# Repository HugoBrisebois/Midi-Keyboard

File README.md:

## Midi-Keyboard

This is my first hardware project. A small and Functional Midi Keyboard

# renders of the project

# features
This Midi Keyboard has two potentiometers, 30 keys for the keyboard itself and for other settings!
- output for AUX
- powered by the Orpheus pico made by Hackclub
- LCD display for menus and feedback
- Custom PCB
- Custom Case

# Software used
- kicad 9.0
- fusion 360
- hackclub Slack for help and questions
- mouser.ca for screws

# Why I made it
I made this Project for Blueprint Hackclub which is a hardware YSWS (You Ship, We Ship) where I will get a grant to buy all the parts I need to build. i built this to get a feel for the YSWS and to learn some hardware

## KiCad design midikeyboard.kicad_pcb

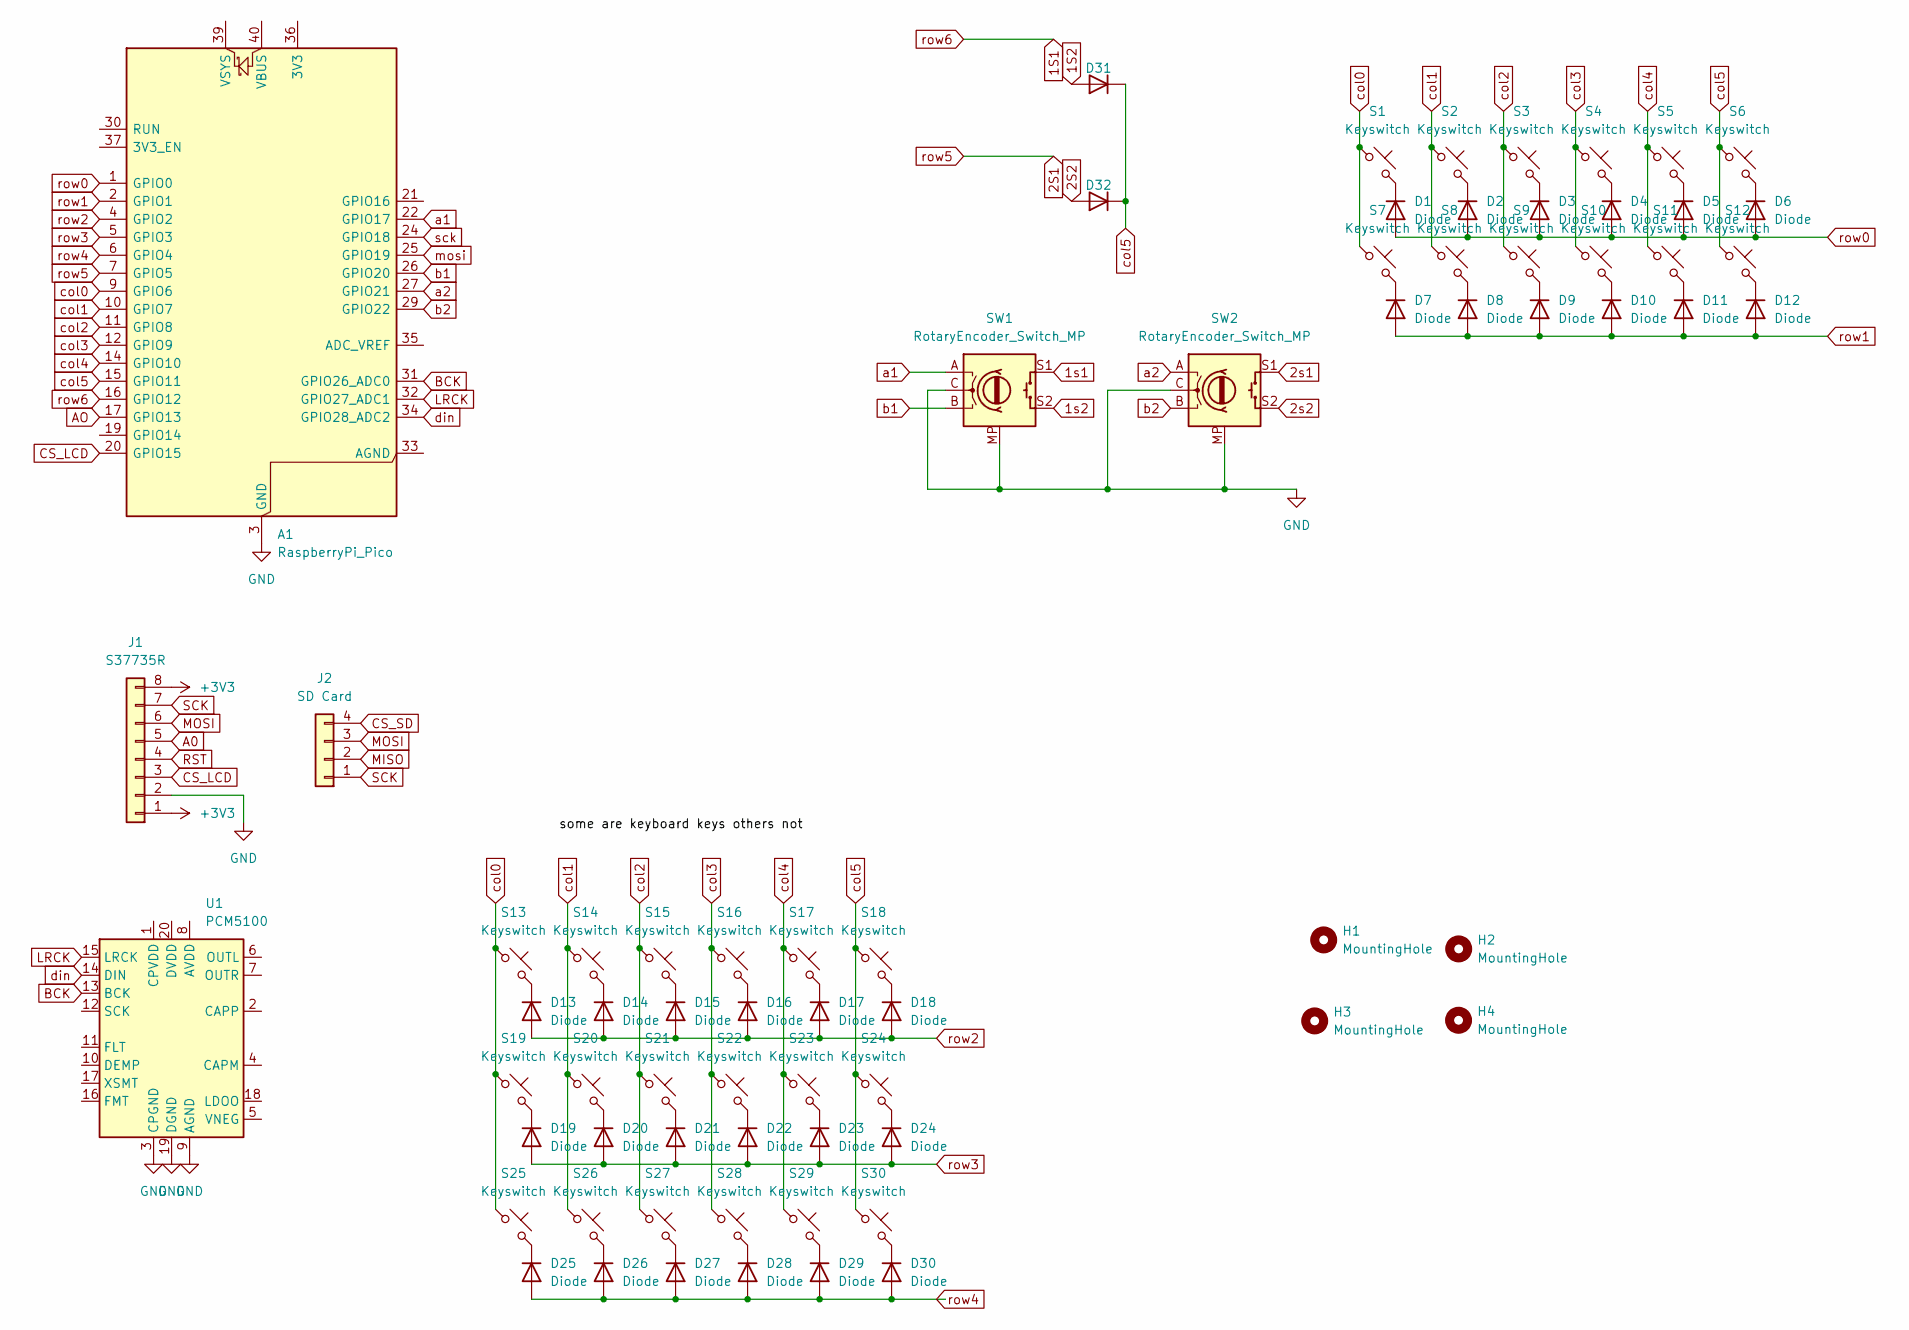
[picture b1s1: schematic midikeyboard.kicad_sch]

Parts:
A1: RaspberryPi_Pico; RaspberryPi_Pico_Common_Unspecified
D1, D2, D3, D4, D5, D6, D7, D8, D9, D10, D11, D12, D13, D14, D15, D16, D17, D18, D19, D20, D21, D22, D23, D24, D25, D26, D27, D28, D29, D30: Diode; Diode_DO-35
D31, D32: 1N4148; Diode_DO-35
H1, H2, H3, H4: MountingHole; MountingHole_3.2mm_M3
J1: S37735R; PinSocket_1x08_P2.54mm_Vertical
J2: SD Card; PinSocket_1x04_P2.54mm_Vertical
S1, S2, S3, S4, S5, S6, S7, S8, S9, S10, S11, S12, S13, S14, S15, S16, S17, S18, S19, S20, S21, S22, S23, S24, S25, S26, S27, S28, S29, S30: Keyswitch; MX_PCB_1.00u
SW1, SW2: RotaryEncoder_Switch_MP; RotaryEncoder_Alps_EC11E-Switch_Vertical_H20mm
U1: PCM5100; PCM5100 I2S DAC

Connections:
1S1: A1.16 (GPIO12)
1S2: D31.2 (A)
1s1: SW1.S1
1s2: SW1.S2
2S1: A1.7 (GPIO5)
2S2: D32.2 (A)
2s1: SW2.S1
2s2: SW2.S2
+3V3: J1.1, J1.8
A0: J1.5
AO: A1.17 (GPIO13)
BCK: A1.31 (GPIO26_ADC0), U1.13 (BCK)
CS_LCD: A1.20 (GPIO15), J1.3
CS_SD: J2.4
GND: A1.3 (GND), A1.8 (GND), A1.13 (GND), A1.18 (GND), A1.23 (GND), A1.28 (GND), A1.38 (GND), J1.2, SW1.C, SW1.MP, SW2.C, SW2.MP, U1.3 (CPGND), U1.9 (AGND), U1.19 (DGND)
LRCK: A1.32 (GPIO27_ADC1), U1.15 (LRCK)
MISO: J2.2
MOSI: J1.6, J2.3
unnamed: D1.1 (K), S1.2
unnamed: D2.1 (K), S2.2
unnamed: D3.1 (K), S3.2
unnamed: D4.1 (K), S4.2
unnamed: D5.1 (K), S5.2
unnamed: D6.1 (K), S6.2
unnamed: D7.1 (K), S7.2
unnamed: D8.1 (K), S8.2
unnamed: D9.1 (K), S9.2
unnamed: D10.1 (K), S10.2
unnamed: D11.1 (K), S11.2
unnamed: D12.1 (K), S12.2
unnamed: D13.1 (K), S13.2
unnamed: D14.1 (K), S14.2
unnamed: D15.1 (K), S15.2
unnamed: D16.1 (K), S16.2
unnamed: D17.1 (K), S17.2
unnamed: D18.1 (K), S18.2
unnamed: D19.1 (K), S19.2
unnamed: D20.1 (K), S20.2
unnamed: D21.1 (K), S21.2
unnamed: D22.1 (K), S22.2
unnamed: D23.1 (K), S23.2
unnamed: D24.1 (K), S24.2
unnamed: D25.1 (K), S25.2
unnamed: D26.1 (K), S26.2
unnamed: D27.1 (K), S27.2
unnamed: D28.1 (K), S28.2
unnamed: D29.1 (K), S29.2
unnamed: D30.1 (K), S30.2
RST: J1.4
SCK: J1.7, J2.1
a1: A1.22 (GPIO17), SW1.A
a2: A1.27 (GPIO21), SW2.A
b1: A1.26 (GPIO20), SW1.B
b2: A1.29 (GPIO22), SW2.B
col0: A1.9 (GPIO6), S1.1, S7.1, S13.1, S19.1, S25.1
col1: A1.10 (GPIO7), S2.1, S8.1, S14.1, S20.1, S26.1
col2: A1.11 (GPIO8), S3.1, S9.1, S15.1, S21.1, S27.1
col3: A1.12 (GPIO9), S4.1, S10.1, S16.1, S22.1, S28.1
col4: A1.14 (GPIO10), S5.1, S11.1, S17.1, S23.1, S29.1
col5: A1.15 (GPIO11), D31.1 (K), D32.1 (K), S6.1, S12.1, S18.1, S24.1, S30.1
din: A1.34 (GPIO28_ADC2), U1.14 (DIN)
mosi: A1.25 (GPIO19)
row0: A1.1 (GPIO0), D1.2 (A), D2.2 (A), D3.2 (A), D4.2 (A), D5.2 (A), D6.2 (A)
row1: A1.2 (GPIO1), D7.2 (A), D8.2 (A), D9.2 (A), D10.2 (A), D11.2 (A), D12.2 (A)
row2: A1.4 (GPIO2), D13.2 (A), D14.2 (A), D15.2 (A), D16.2 (A), D17.2 (A), D18.2 (A)
row3: A1.5 (GPIO3), D19.2 (A), D20.2 (A), D21.2 (A), D22.2 (A), D23.2 (A), D24.2 (A)
row4: A1.6 (GPIO4), D25.2 (A), D26.2 (A), D27.2 (A), D28.2 (A), D29.2 (A), D30.2 (A)
sck: A1.24 (GPIO18)

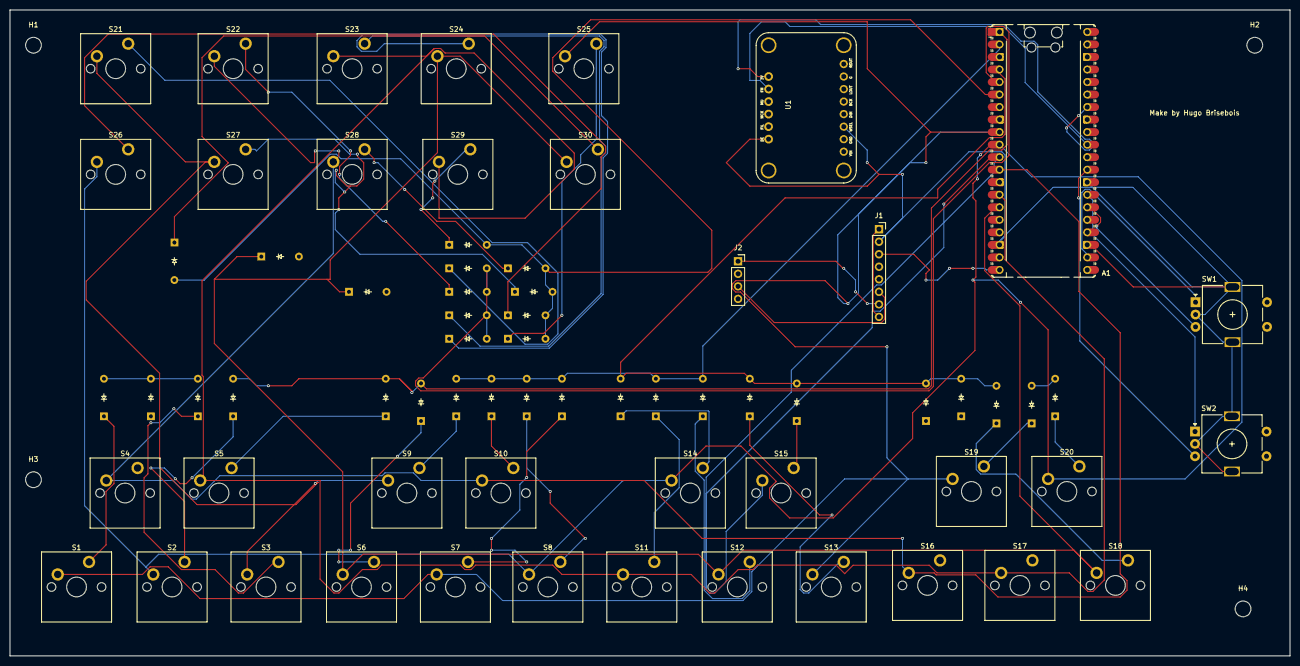
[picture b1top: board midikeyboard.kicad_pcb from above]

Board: 2 copper layers, 259.6 x 131.0 mm, 72 parts (0 on the bottom side), 52 nets.

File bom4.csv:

Reference,Qty,value,,footprint,datasheet,,price $,,purchase link
A1,1,Orpheus Pico,,Module:RaspberryPi_Pico_Common_Unspecified,https://datasheets.raspberrypi.com/pico/pico-datasheet.pdf,,N/A (PROVIDED IN KIT),,
"D1,D2,D3,D4,D5,D6,D7,D8,D9,10,D11,D12,D13,D14,D15,D16,D17,D18,D19,D20,D21,D22,D23,D24,D25,D26,D27,D28,D29,D30,D32",30, 1N4148 & D~,,Diode_THT:D_DO-35_SOD27_P7.62mm_Horizontal,https://assets.nexperia.com/documents/data-sheet/1N4148_1N4448.pdf,,N/A (PROVIDED IN KIT),,
J1,1,S37735R,,Connector_PinSocket_2.54mm:PinSocket_1x08_P2.54mm_Vertical,~,,N/A (PROVIDED IN KIT),,
J2,1,SD CARD,,Connector_PinSocket_2.54mm:PinSocket_1x04_P2.54mm_Vertical,~,,N/A (PROVIDED IN KIT),,
"S1,S2,S3,S4,S5,S6,S7,S8,S9,S10,S11,S12,S13,S14,S15,S16,S17,18,S19,S20,S21,S22,S23,S24,S25,S26,S27,S28,S29,S30",30,KEYSWITCH,,Keyswitch:scottokeebs_mx:mx_PCB_1.00u,~,,N/A (PROVIDED IN KIT),,
"SW1,SW2",2,RotaryEncoder_switch_MP,,Rotary_Encoder:RotaryEncoder_alps_EC11E-switch_vertical_h20mm,,,N/A (PROVIDED IN KIT),,
U2,1,PCM5100,,ScottoKeebs_Scotto:PCM5100 I2S DAC,http://www.ti.com/lit/ds/symlink/pcm5100.pdf,,N/A (PROVIDED IN KIT),,
,,,,,,,,,
,,,,,,,,,
,,,,,,,,,
M3 screws,4,N/A,,Hardware,,,0.79$,,https://www.mouser.ca/ProductDetail/Essentra/50M030050K035?q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
M3 screws,4,N/A,,Hardware,,,0.79$,,https://www.mouser.ca/ProductDetail/Essentra/50M030050K042?q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

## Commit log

2025-10-17 uploaded screen shots of project
2025-10-17 fixing added files
2025-10-18 working on submitting the project
2025-10-18 adding case with pcb
2025-10-19 added 3D model folder
2025-10-19 placed all the PCB files in a folder
2025-10-19 added BOM
2025-10-20 Initialize README with project information
    Added project details, features, and software used for the Midi Keyboard.
